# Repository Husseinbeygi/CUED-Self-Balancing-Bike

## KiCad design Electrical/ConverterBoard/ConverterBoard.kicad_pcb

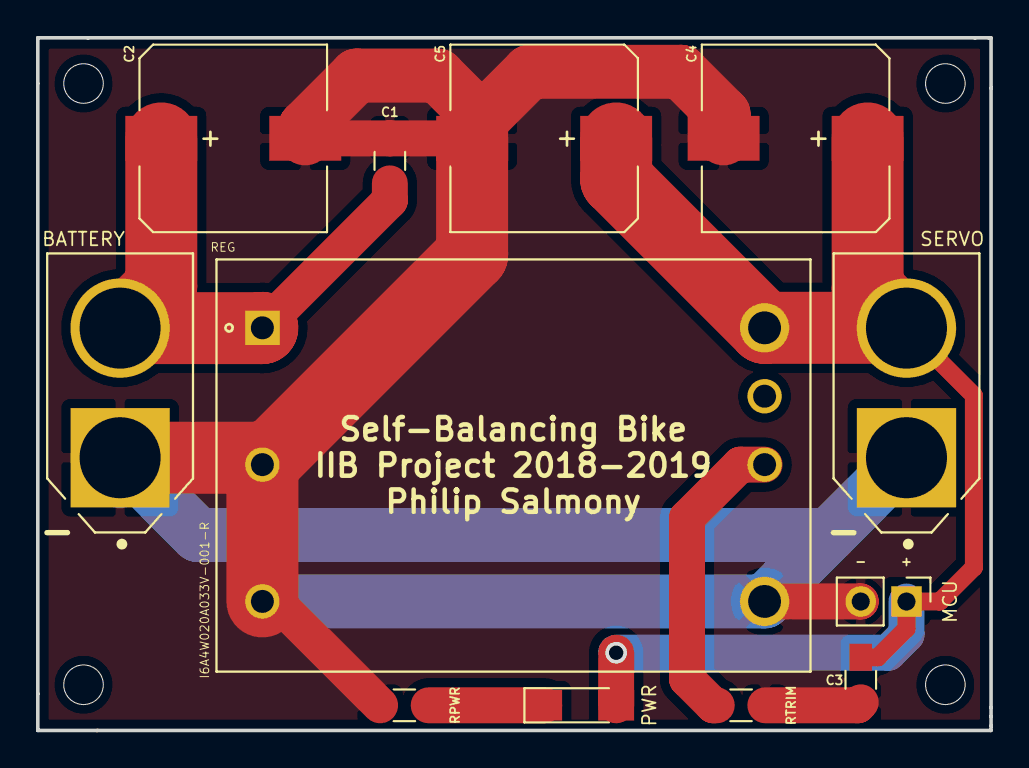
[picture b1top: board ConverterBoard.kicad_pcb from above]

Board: 2 copper layers, 53.0 x 38.5 mm, 12 parts (0 on the bottom side), 5 nets.

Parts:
BATTERY: AMASS_XT60-M
C1, C3: C_0805_HandSoldering
C2, C4, C5: CP_Elec_10x10
MCU: Pin_Header_Straight_1x02_Pitch2.54mm
PWR: LED_1206_HandSoldering
REG: I6A4W020A033V-001-R; TDK-LAMBDA_I6A4W020A033V-001-R
RPWR: R_0805_HandSoldering
RTRIM: R_0805_HandSoldering
SERVO: AMASS_XT60-M

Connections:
+12V: C3.1, C4.1, C5.1, MCU.1, PWR.2, REG.8, SERVO.2
GND: BATTERY.1, C1.2, C2.2, C3.2, C4.2, C5.2, MCU.2, REG.2, REG.3, REG.4, RPWR.1, RTRIM.1, SERVO.1
unnamed: PWR.1, RPWR.2
unnamed: REG.6, RTRIM.2
VCC: BATTERY.2, C1.1, C2.1, REG.1

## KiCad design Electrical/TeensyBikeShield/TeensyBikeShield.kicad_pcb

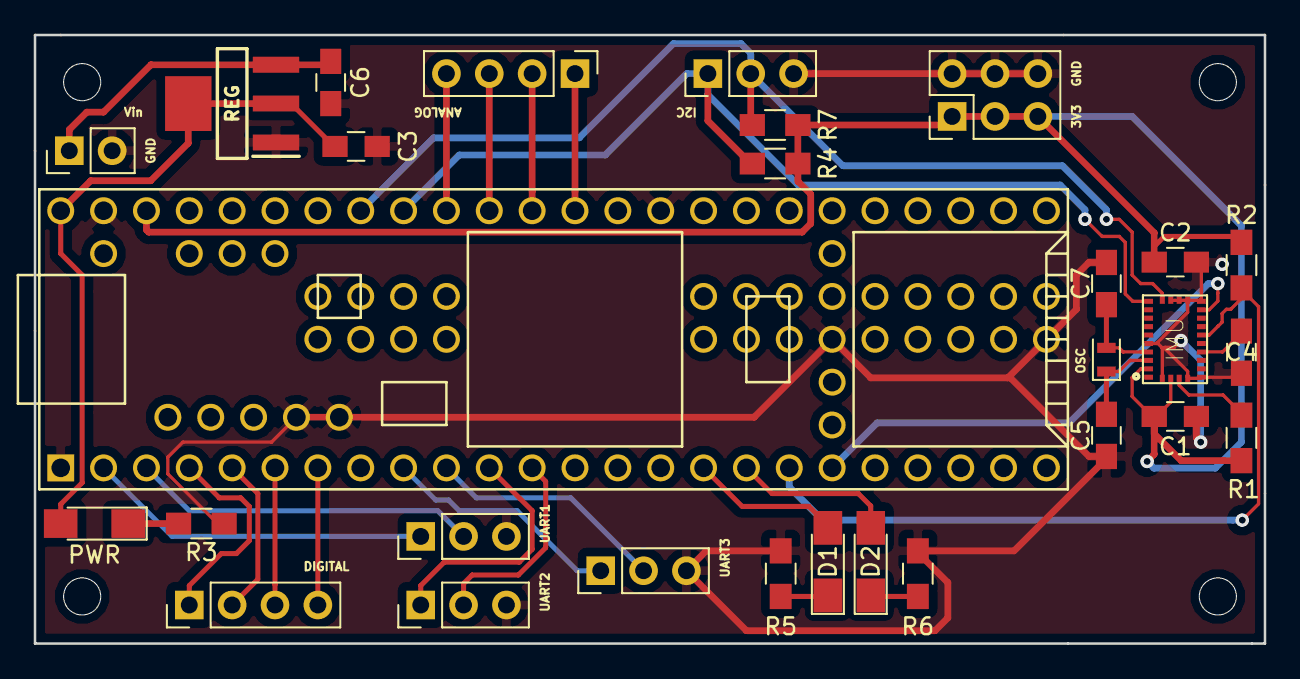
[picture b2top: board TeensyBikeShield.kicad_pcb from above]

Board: 2 copper layers, 72.9 x 36.1 mm, 27 parts (0 on the bottom side), 14 nets.

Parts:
ANALOG: Pin_Header_Straight_1x04_Pitch2.54mm
C1, C2, C3, C4, C5, C6, C7: C_0805_HandSoldering
D1, D2: LED_1206_HandSoldering
DIGITAL: Pin_Header_Straight_1x04_Pitch2.54mm
I2C: Pin_Header_Straight_1x03_Pitch2.54mm
IMU: LGA28R50P4X10_380X520X100
OSC: Crystal_SMD_2012-2pin_2.0x1.2mm
PWR: LED_1206_HandSoldering
R1, R2, R3, R4, R5, R6, R7: R_0805_HandSoldering
REG: LDL1117S50R; SOT230P700X180-4N
UART1, UART2, UART3: Pin_Header_Straight_1x03_Pitch2.54mm
Vin: Pin_Header_Straight_1x02_Pitch2.54mm

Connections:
+3V3: C1.1, C2.1, IMU.3, IMU.28, R1.2, R2.2, R4.2, R7.2
+5V: C3.1, PWR.2, REG.2, REG.4
/I2C_SCL: I2C.2, IMU.19, R7.1
/I2C_SDA: I2C.1, IMU.20, R4.1
/IMU_RESET: IMU.11, R2.1
/XIN32: C5.1, IMU.27, OSC.1
/XOUT32: C7.1, IMU.26, OSC.2
GND: C1.2, C2.2, C3.2, C4.2, C5.2, C6.2, C7.2, I2C.3, IMU.2, IMU.5, IMU.6, IMU.15, IMU.16, IMU.17, IMU.18, IMU.25, R3.1, R5.1, R6.1, REG.1, UART1.3, UART2.3, UART3.3, Vin.2
unnamed: C4.1, IMU.9
unnamed: D1.1, R5.2
unnamed: D2.1, R6.2
unnamed: IMU.4, R1.1
unnamed: PWR.1, R3.2
VCC: C6.1, REG.3, Vin.1

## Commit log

2019-05-21 Wrote a bit more...
2019-05-21 And even more...
2019-05-21 Next revision.
2019-05-22 Started on section FS implementation.
2019-05-22 Started on FS implementation section.
2019-05-24 FS implementation and conclusions.
2019-05-27 FS and abstract.
2019-05-28 Final changes to report.
